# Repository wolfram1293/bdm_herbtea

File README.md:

# bdm_herbtea

## GUIフレームワーク案

### Electron
Webの技術（HTMLやJavaScript）で作ったものをデスクトップアプリケーション化できる
npmからインストール
- https://qiita.com/umamichi/items/6ce4f46c1458e89c4cfc
- https://www.pc-koubou.jp/magazine/23739

### Kivy
PythonのGUIライブラリの中でもっとも人気らしい
CSSっぽい独自の言語でスタイル記述をするらしい
- http://independence-sys.net/main/?p=4315

### Pygame
本来はゲーム作成に特化したライブラリ
タッチアプリのサンプルで書いてたやつ
- https://www.simugrammer.com/python_pygame_introduction/

## プレゼン

### イントロ
わたくし達お嬢様ですので、毎日優雅にハーブティーを嗜んでおりますわ()
- いちいち計量してブレンドするのは面倒くさい
- ブレンドの種類も効果も多すぎて大変  
→効果からブレンドを選ぶと自動で計量、ブレンドした茶葉を出してくれる機械

### 使い方
- 前面のタッチパネルでブレンドを選択してブレンドボタンを押すだけ  
→実演

### ハードウェア
- ラズパイ、モータードライバ  
→タッチパネルから入力、GPIO端子からモータードライバを制御

- タッチパネル  
→最新家電のようにパネルで情報を表示、タッチで直感的操作が可能

- 螺旋式ディスペンサー  
→一定量ずつ出るので各茶葉ごとに時間で計量できる

### ソフトウェア
- Kivy
- フレームワークの説明、実用例など

### 応用例
- 粉末〜粒状のものをブレンドするのにはなんでも使える  
→紅茶、スパイスなどのブレンドにも

### 実演
- 現地でできたら先生に好みを聞いてブレンドしてプレゼント

## ブレンド例

### カモミール ラベンダー
リラックス 安眠

### ローズ マローブルー
美容 整腸作用

### カモミール マローブルー
リラックス 整腸作用

### ローズ カモミール
美容 リラックス

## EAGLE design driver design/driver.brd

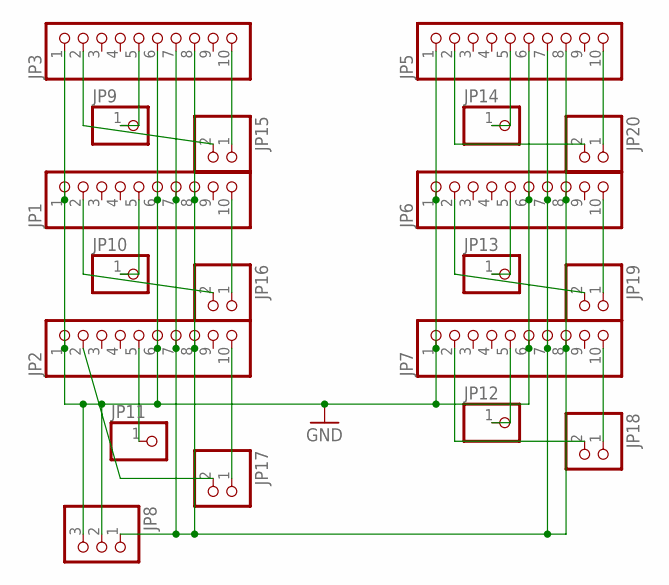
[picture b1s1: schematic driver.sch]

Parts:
JP1, JP2, JP3, JP5, JP6, JP7: PINHD-1X10; 1X10
JP8: PINHD-1X3; 1X03
JP9, JP10, JP11, JP12, JP13, JP14: PINHD-1X1; 1X01
JP15, JP16, JP17, JP18, JP19, JP20: PINHD-1X2; 1X02

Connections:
GND: JP1.1, JP1.6, JP2.1, JP2.6, JP3.1, JP3.6, JP5.1, JP5.6, JP6.1, JP6.6, JP7.1, JP7.6, JP8.2, JP8.3
unnamed: JP2.5, JP11.1
unnamed: JP3.5, JP9.1
unnamed: JP3.2, JP15.2
unnamed: JP3.10, JP15.1
unnamed: JP5.2, JP20.2
unnamed: JP1.5, JP10.1
unnamed: JP2.2, JP17.2
unnamed: JP2.10, JP17.1
unnamed: JP7.5, JP12.1
unnamed: JP6.5, JP13.1
unnamed: JP5.5, JP14.1
unnamed: JP1.10, JP16.1
unnamed: JP1.7, JP1.8, JP2.7, JP2.8, JP3.7, JP3.8, JP5.7, JP5.8, JP6.7, JP6.8, JP7.7, JP7.8, JP8.1
unnamed: JP1.2, JP16.2
unnamed: JP5.10, JP20.1
unnamed: JP6.10, JP19.1
unnamed: JP7.10, JP18.1
unnamed: JP7.2, JP18.2
unnamed: JP6.2, JP19.2

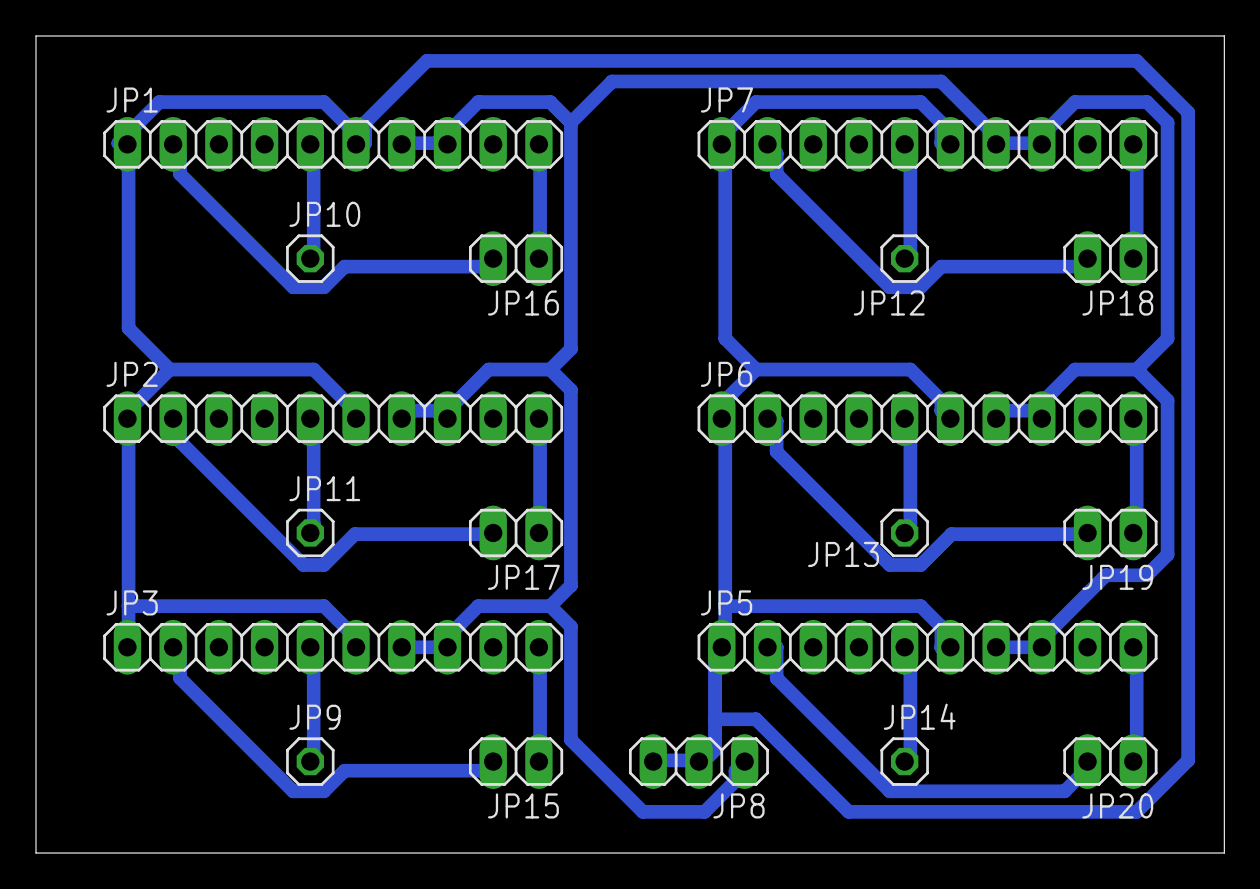
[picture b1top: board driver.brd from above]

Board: 2 copper layers, 66.0 x 45.4 mm, 19 parts (0 on the bottom side), 20 nets.

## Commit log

2020-12-09 first commit by Keigo Yonezawa
2020-12-09 add sample
2020-12-09 comment out line 40,41
2020-12-09 add line 86 in touch_gui.py
2020-12-09 add line 32~44 in bdm_~~_moter.py
2020-12-09 add angle option
2020-12-21 add bdm_mode_dcmoter.py
2020-12-21 bug fixed
2020-12-21 change val
2020-12-21 change val 5000
2020-12-22 add AppName~~.zip
2020-12-22 add driver design
2020-12-23 add move_~~_20.py & move_~~_21.py
2020-12-23 add gpio18
2020-12-24 add bdm_~~_gpio12.py and bdm_~~_gpio16.py
2020-12-27 innstall request
2020-12-27 unzip
2020-12-27 add packaged files
2020-12-27 change loadURL
2020-12-27 fixed
2020-12-29 add app_2020-1228
2020-12-29 changed index.html in app_2020-1228
2020-12-29 add packaged app
2020-12-29 add debug print
2021-01-04 add presentation script
2021-01-04 add script
2021-01-04 fixed readme
2021-01-05 add kivy_app
2021-01-05 change kivy_app/app_sample/main.py
2021-01-06 changed kivy_app
2021-01-06 add blend
2021-01-06 add pict
2021-01-07 add images
